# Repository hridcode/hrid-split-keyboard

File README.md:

# hrid's split keyboard

hrid's split keyboard is a sleek, custom staggered ortholinear wireless split keyboard that runs off the ESP32-S3-WROOM SMD module.

# Features

- OLED display
- EC11 rotary encoder w/ button
- Hot-swappable key switches
- Exposed circuitry look w/ acrylic top plate
- USB-C charging
- 2000mAh li-ion battery
- ESP32-S3-WROOM-1 MCU

# Photos

|Schematic|PCB|Case|
|---|---|---|
||||

# Notes

I'm not sure if this WILL work because I've heard KMK has bad support for BLE split keebs, and there may be some potential issues with the ESP32-S3-WROOM.

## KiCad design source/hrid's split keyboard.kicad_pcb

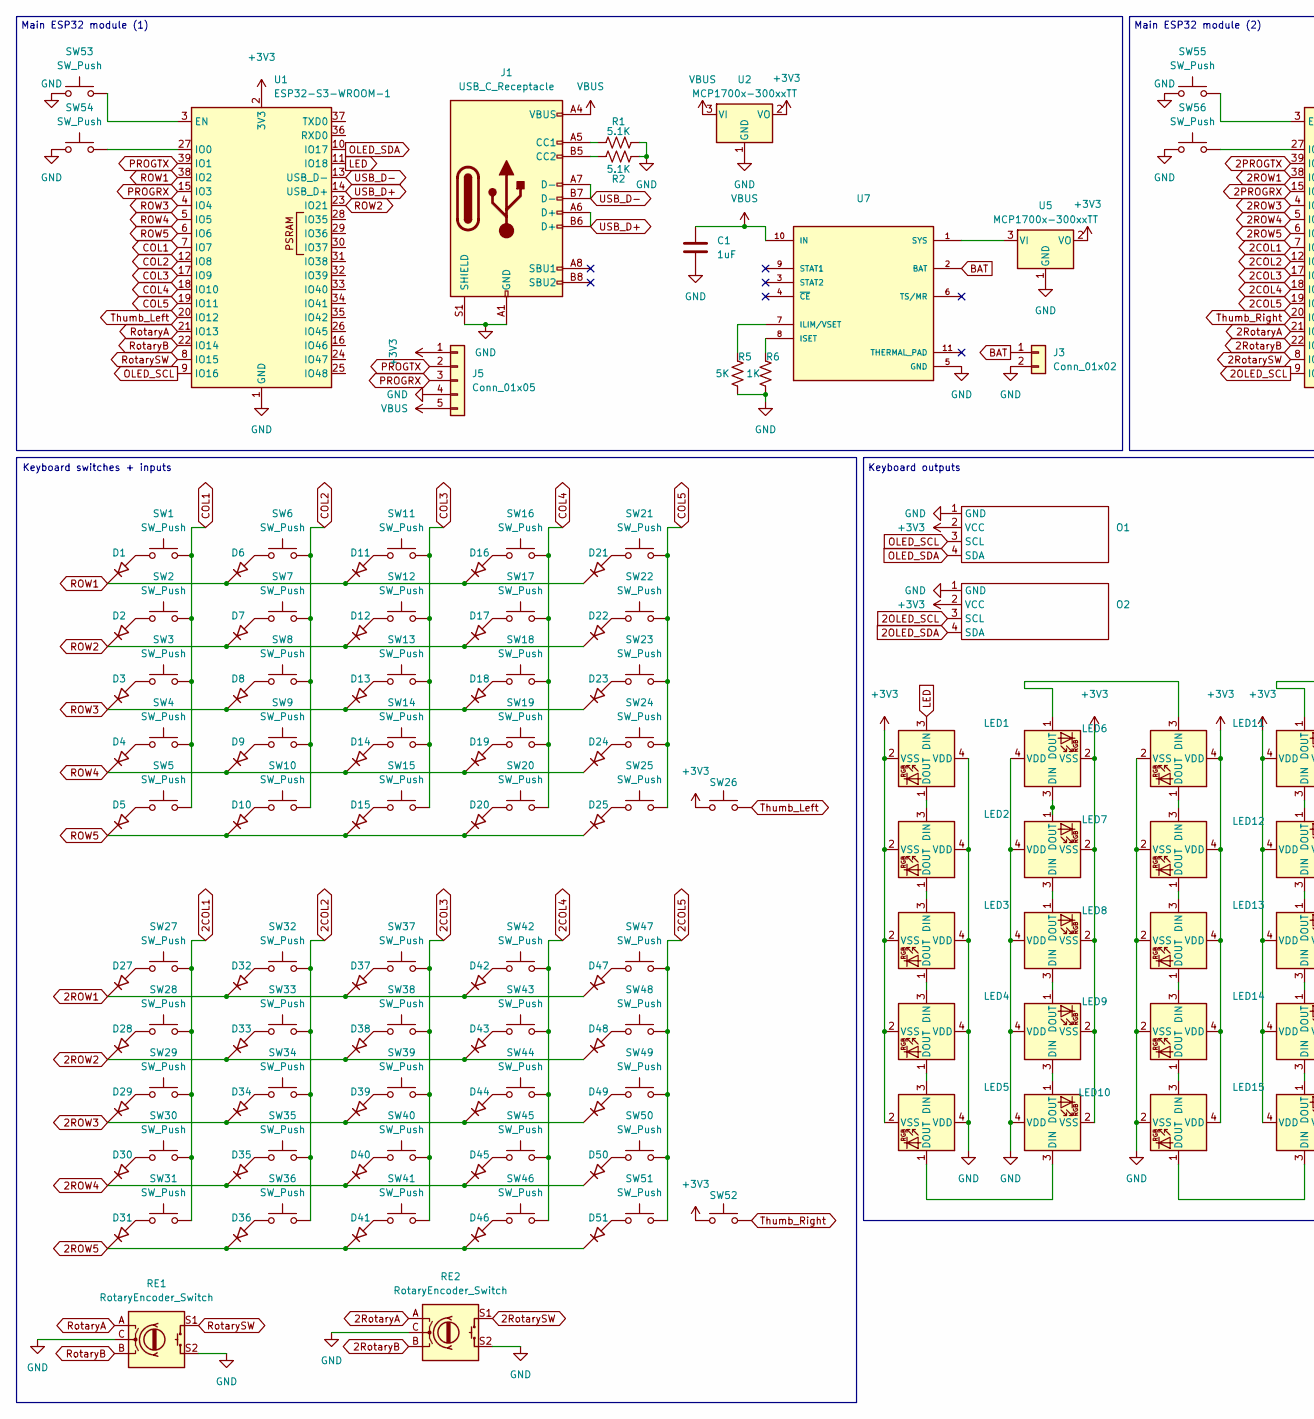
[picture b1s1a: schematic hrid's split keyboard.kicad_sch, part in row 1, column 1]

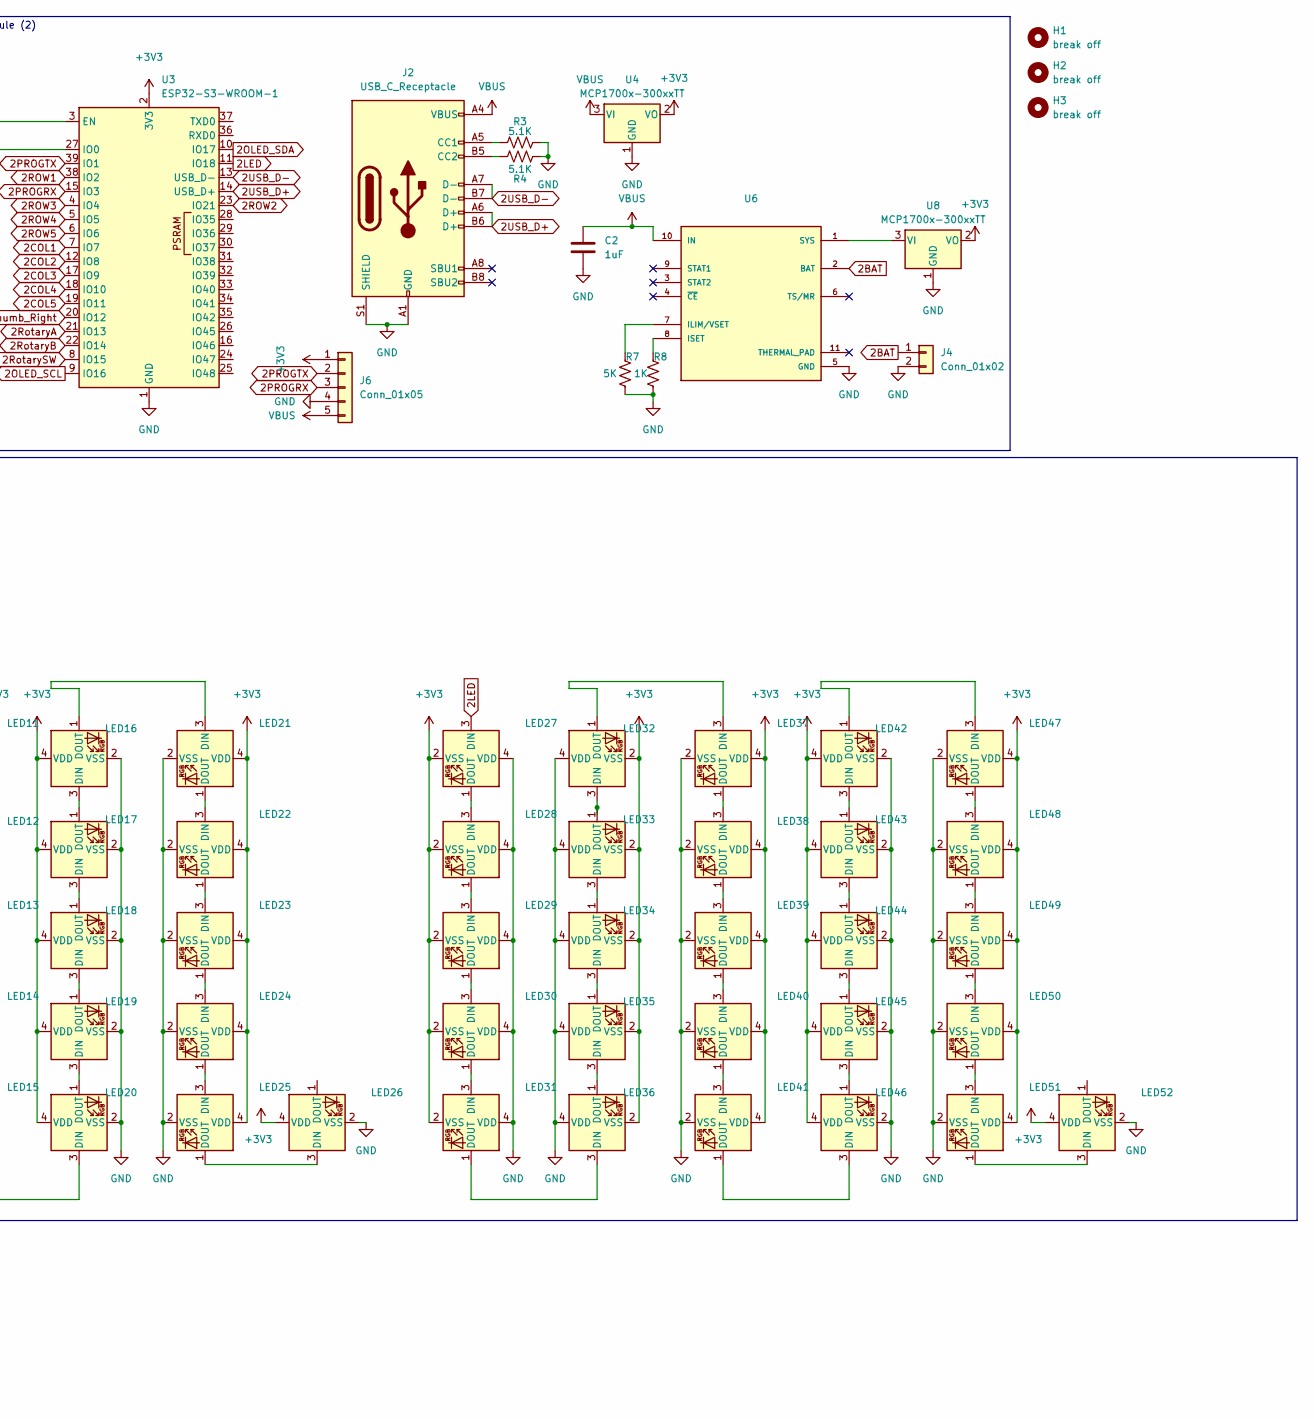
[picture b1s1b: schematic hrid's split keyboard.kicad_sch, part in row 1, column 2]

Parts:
C1, C2: 1uF; C_0603_1608Metric
D1, D2, D3, D4, D5, D6, D7, D8, D9, D10, D11, D12, D13, D14, D15, D16, D17, D18, D19, D20, D21, D22, D23, D24, D25, D27, D28, D29, D30, D31, D32, D33, D34, D35, D36, D37, D38, D39, D40, D41, D42, D43, D44, D45, D46, D47, D48, D49, D50, D51: D_45deg; D_0402_1005Metric_Pad0.77x0.64mm_HandSolder
H1, H2, H3: break off; MouseBite-Part_2.0x4.5mm_outset_D0.5mm_P0.85mm_7h
J1, J2: USB_C_Receptacle; USB_C_Receptacle_HRO_TYPE-C-31-M-12
J3, J4: Conn_01x02; JST_EH_S2B-EH_1x02_P2.50mm_Horizontal
J5, J6: Conn_01x05; PinHeader_1x05_P2.54mm_Vertical
LED1, LED2, LED3, LED4, LED5, LED6, LED7, LED8, LED9, LED10, LED11, LED12, LED13, LED14, LED15, LED16, LED17, LED18, LED19, LED20, LED21, LED22, LED23, LED24, LED25, LED26, LED27, LED28, LED29, LED30, LED31, LED32, LED33, LED34, LED35, LED36, LED37, LED38, LED39, LED40, LED41, LED42, LED43, LED44, LED45, LED46, LED47, LED48, LED49, LED50, LED51, LED52: SK6812MINI; LED_SK6812MINI_PLCC4_3.5x3.5mm_P1.75mm
O1, O2: SSD1306-4pin-0.91
R1, R2, R3, R4: 5.1K; R_0603_1608Metric
R5, R7: 5K; R_0603_1608Metric
R6, R8: 1K; R_0603_1608Metric
RE1, RE2: RotaryEncoder_Switch; RotaryEncoder_Alps_EC11E-Switch_Vertical_H20mm_MountingHoles
SW1, SW2, SW3, SW4, SW5, SW6, SW7, SW8, SW9, SW10, SW11, SW12, SW13, SW14, SW15, SW16, SW17, SW18, SW19, SW20, SW21, SW22, SW23, SW24, SW25, SW26, SW27, SW28, SW29, SW30, SW31, SW32, SW33, SW34, SW35, SW36, SW37, SW38, SW39, SW40, SW41, SW42, SW43, SW44, SW45, SW46, SW47, SW48, SW49, SW50, SW51, SW52: SW_Push; SW_MX_HotSwap_THT
SW53, SW54, SW55, SW56: SW_Push; D_2114_3652Metric
U1, U3: ESP32-S3-WROOM-1
U2, U4, U5, U8: MCP1700x-300xxTT; SOT-23
U6, U7: WSON-10-1EP_4x3mm_P0.5mm_EP2.2x2mm

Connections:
2BAT: J4.1, U6.2 (BAT)
2COL1: SW27.2, SW28.2, SW29.2, SW30.2, SW31.2, U3.7 (IO7)
2COL2: SW32.2, SW33.2, SW34.2, SW35.2, SW36.2, U3.12 (IO8)
2COL3: SW37.2, SW38.2, SW39.2, SW40.2, SW41.2, U3.17 (IO9)
2COL4: SW42.2, SW43.2, SW44.2, SW45.2, SW46.2, U3.18 (IO10)
2COL5: SW47.2, SW48.2, SW49.2, SW50.2, SW51.2, U3.19 (IO11)
2LED: LED27.3 (DIN), U3.11 (IO18)
2OLED_SCL: O2.3 (SCL), U3.9 (IO16)
2OLED_SDA: O2.4 (SDA), U3.10 (IO17)
2PROGRX: J6.3, U3.15 (IO3)
2PROGTX: J6.2, U3.39 (IO1)
2ROW1: D27.1 (K), D32.1 (K), D37.1 (K), D42.1 (K), D47.1 (K), U3.38 (IO2)
2ROW2: D28.1 (K), D33.1 (K), D38.1 (K), D43.1 (K), D48.1 (K), U3.23 (IO21)
2ROW3: D29.1 (K), D34.1 (K), D39.1 (K), D44.1 (K), D49.1 (K), U3.4 (IO4)
2ROW4: D30.1 (K), D35.1 (K), D40.1 (K), D45.1 (K), D50.1 (K), U3.5 (IO5)
2ROW5: D31.1 (K), D36.1 (K), D41.1 (K), D46.1 (K), D51.1 (K), U3.6 (IO6)
2RotaryA: RE2.A, U3.21 (IO13)
2RotaryB: RE2.B, U3.22 (IO14)
2RotarySW: RE2.S1, U3.8 (IO15)
2USB_D+: J2.A6 (D+), J2.B6 (D+), U3.14 (USB_D+)
2USB_D-: J2.A7 (D-), J2.B7 (D-), U3.13 (USB_D-)
+3V3: J5.1, J6.1, LED1.2 (VSS), LED2.2 (VSS), LED3.2 (VSS), LED4.2 (VSS), LED5.2 (VSS), LED6.2 (VSS), LED7.2 (VSS), LED8.2 (VSS), LED9.2 (VSS), LED10.2 (VSS), LED11.4 (VDD), LED12.4 (VDD), LED13.4 (VDD), LED14.4 (VDD), LED15.4 (VDD), LED16.4 (VDD), LED17.4 (VDD), LED18.4 (VDD), LED19.4 (VDD), LED20.4 (VDD), LED21.4 (VDD), LED22.4 (VDD), LED23.4 (VDD), LED24.4 (VDD), LED25.4 (VDD), LED26.4 (VDD), LED27.2 (VSS), LED28.2 (VSS), LED29.2 (VSS), LED30.2 (VSS), LED31.2 (VSS), LED32.2 (VSS), LED33.2 (VSS), LED34.2 (VSS), LED35.2 (VSS), LED36.2 (VSS), LED37.4 (VDD), LED38.4 (VDD), LED39.4 (VDD), LED40.4 (VDD), LED41.4 (VDD), LED42.4 (VDD), LED43.4 (VDD), LED44.4 (VDD), LED45.4 (VDD), LED46.4 (VDD), LED47.4 (VDD), LED48.4 (VDD), LED49.4 (VDD), LED50.4 (VDD), LED51.4 (VDD), LED52.4 (VDD), O1.2 (VCC), O2.2 (VCC), SW26.1, SW52.1, U1.2 (3V3), U2.2 (VO), U3.2 (3V3), U4.2 (VO), U5.2 (VO), U8.2 (VO)
BAT: J3.1, U7.2 (BAT)
COL1: SW1.2, SW2.2, SW3.2, SW4.2, SW5.2, U1.7 (IO7)
COL2: SW6.2, SW7.2, SW8.2, SW9.2, SW10.2, U1.12 (IO8)
COL3: SW11.2, SW12.2, SW13.2, SW14.2, SW15.2, U1.17 (IO9)
COL4: SW16.2, SW17.2, SW18.2, SW19.2, SW20.2, U1.18 (IO10)
COL5: SW21.2, SW22.2, SW23.2, SW24.2, SW25.2, U1.19 (IO11)
GND: C1.2, C2.2, J1.A1 (GND), J1.A12 (GND), J1.B1 (GND), J1.B12 (GND), J1.S1 (SHIELD), J2.A1 (GND), J2.A12 (GND), J2.B1 (GND), J2.B12 (GND), J2.S1 (SHIELD), J3.2, J4.2, J5.4, J6.4, LED1.4 (VDD), LED2.4 (VDD), LED3.4 (VDD), LED4.4 (VDD), LED5.4 (VDD), LED6.4 (VDD), LED7.4 (VDD), LED8.4 (VDD), LED9.4 (VDD), LED10.4 (VDD), LED11.2 (VSS), LED12.2 (VSS), LED13.2 (VSS), LED14.2 (VSS), LED15.2 (VSS), LED16.2 (VSS), LED17.2 (VSS), LED18.2 (VSS), LED19.2 (VSS), LED20.2 (VSS), LED21.2 (VSS), LED22.2 (VSS), LED23.2 (VSS), LED24.2 (VSS), LED25.2 (VSS), LED26.2 (VSS), LED27.4 (VDD), LED28.4 (VDD), LED29.4 (VDD), LED30.4 (VDD), LED31.4 (VDD), LED32.4 (VDD), LED33.4 (VDD), LED34.4 (VDD), LED35.4 (VDD), LED36.4 (VDD), LED37.2 (VSS), LED38.2 (VSS), LED39.2 (VSS), LED40.2 (VSS), LED41.2 (VSS), LED42.2 (VSS), LED43.2 (VSS), LED44.2 (VSS), LED45.2 (VSS), LED46.2 (VSS), LED47.2 (VSS), LED48.2 (VSS), LED49.2 (VSS), LED50.2 (VSS), LED51.2 (VSS), LED52.2 (VSS), O1.1 (GND), O2.1 (GND), R1.2, R2.2, R3.2, R4.2, R5.2, R6.2, R7.2, R8.2, RE1.C, RE1.S2, RE2.C, RE2.S2, SW53.1, SW54.1, SW55.1, SW56.1, U1.1 (GND), U1.40 (GND), U1.41 (GND), U2.1 (GND), U3.1 (GND), U3.40 (GND), U3.41 (GND), U4.1 (GND), U5.1 (GND), U6.5 (GND), U7.5 (GND), U8.1 (GND)
LED: LED1.3 (DIN), U1.11 (IO18)
unnamed: D1.2 (A), SW1.1
unnamed: D2.2 (A), SW2.1
unnamed: D3.2 (A), SW3.1
unnamed: D4.2 (A), SW4.1
unnamed: D5.2 (A), SW5.1
unnamed: D6.2 (A), SW6.1
unnamed: D7.2 (A), SW7.1
unnamed: D8.2 (A), SW8.1
unnamed: D9.2 (A), SW9.1
unnamed: D10.2 (A), SW10.1
unnamed: D11.2 (A), SW11.1
unnamed: D12.2 (A), SW12.1
unnamed: D13.2 (A), SW13.1
unnamed: D14.2 (A), SW14.1
unnamed: D15.2 (A), SW15.1
unnamed: D16.2 (A), SW16.1
unnamed: D17.2 (A), SW17.1
unnamed: D18.2 (A), SW18.1
unnamed: D19.2 (A), SW19.1
unnamed: D20.2 (A), SW20.1
unnamed: D21.2 (A), SW21.1
unnamed: D22.2 (A), SW22.1
unnamed: D23.2 (A), SW23.1
unnamed: D24.2 (A), SW24.1
unnamed: D25.2 (A), SW25.1
unnamed: D27.2 (A), SW27.1
unnamed: D28.2 (A), SW28.1
unnamed: D29.2 (A), SW29.1
unnamed: D30.2 (A), SW30.1
unnamed: D31.2 (A), SW31.1
unnamed: D32.2 (A), SW32.1
unnamed: D33.2 (A), SW33.1
unnamed: D34.2 (A), SW34.1
unnamed: D35.2 (A), SW35.1
unnamed: D36.2 (A), SW36.1
unnamed: D37.2 (A), SW37.1
unnamed: D38.2 (A), SW38.1
unnamed: D39.2 (A), SW39.1
unnamed: D40.2 (A), SW40.1
unnamed: D41.2 (A), SW41.1
unnamed: D42.2 (A), SW42.1
unnamed: D43.2 (A), SW43.1
unnamed: D44.2 (A), SW44.1
unnamed: D45.2 (A), SW45.1
unnamed: D46.2 (A), SW46.1
unnamed: D47.2 (A), SW47.1
unnamed: D48.2 (A), SW48.1
unnamed: D49.2 (A), SW49.1
unnamed: D50.2 (A), SW50.1
unnamed: D51.2 (A), SW51.1
unnamed: J1.A5 (CC1), R1.1
unnamed: J1.B5 (CC2), R2.1
unnamed: J2.A5 (CC1), R3.1
unnamed: J2.B5 (CC2), R4.1
unnamed: LED1.1 (DOUT), LED2.3 (DIN)
unnamed: LED2.1 (DOUT), LED3.3 (DIN)
unnamed: LED3.1 (DOUT), LED4.3 (DIN)
unnamed: LED4.1 (DOUT), LED5.3 (DIN)
unnamed: LED6.3 (DIN), LED7.1 (DOUT)
unnamed: LED7.3 (DIN), LED8.1 (DOUT)
unnamed: LED8.3 (DIN), LED9.1 (DOUT)
unnamed: LED5.1 (DOUT), LED10.3 (DIN)
unnamed: LED9.3 (DIN), LED10.1 (DOUT)
unnamed: LED6.1 (DOUT), LED11.3 (DIN)
unnamed: LED11.1 (DOUT), LED12.3 (DIN)
unnamed: LED12.1 (DOUT), LED13.3 (DIN)
unnamed: LED13.1 (DOUT), LED14.3 (DIN)
unnamed: LED14.1 (DOUT), LED15.3 (DIN)
unnamed: LED15.1 (DOUT), LED20.3 (DIN)
unnamed: LED16.3 (DIN), LED17.1 (DOUT)
unnamed: LED16.1 (DOUT), LED21.3 (DIN)
unnamed: LED17.3 (DIN), LED18.1 (DOUT)
unnamed: LED18.3 (DIN), LED19.1 (DOUT)
unnamed: LED19.3 (DIN), LED20.1 (DOUT)
unnamed: LED21.1 (DOUT), LED22.3 (DIN)
unnamed: LED22.1 (DOUT), LED23.3 (DIN)
unnamed: LED23.1 (DOUT), LED24.3 (DIN)
unnamed: LED24.1 (DOUT), LED25.3 (DIN)
unnamed: LED25.1 (DOUT), LED26.3 (DIN)
unnamed: LED27.1 (DOUT), LED28.3 (DIN)
unnamed: LED28.1 (DOUT), LED29.3 (DIN)
unnamed: LED29.1 (DOUT), LED30.3 (DIN)
unnamed: LED30.1 (DOUT), LED31.3 (DIN)
unnamed: LED31.1 (DOUT), LED36.3 (DIN)
unnamed: LED32.3 (DIN), LED33.1 (DOUT)
unnamed: LED32.1 (DOUT), LED37.3 (DIN)
unnamed: LED33.3 (DIN), LED34.1 (DOUT)
unnamed: LED34.3 (DIN), LED35.1 (DOUT)
unnamed: LED35.3 (DIN), LED36.1 (DOUT)
unnamed: LED37.1 (DOUT), LED38.3 (DIN)
unnamed: LED38.1 (DOUT), LED39.3 (DIN)
unnamed: LED39.1 (DOUT), LED40.3 (DIN)
unnamed: LED40.1 (DOUT), LED41.3 (DIN)
unnamed: LED41.1 (DOUT), LED46.3 (DIN)
unnamed: LED42.3 (DIN), LED43.1 (DOUT)
unnamed: LED42.1 (DOUT), LED47.3 (DIN)
unnamed: LED43.3 (DIN), LED44.1 (DOUT)
unnamed: LED44.3 (DIN), LED45.1 (DOUT)
unnamed: LED45.3 (DIN), LED46.1 (DOUT)
unnamed: LED47.1 (DOUT), LED48.3 (DIN)
unnamed: LED48.1 (DOUT), LED49.3 (DIN)
unnamed: LED49.1 (DOUT), LED50.3 (DIN)
unnamed: LED50.1 (DOUT), LED51.3 (DIN)
unnamed: LED51.1 (DOUT), LED52.3 (DIN)
unnamed: SW53.2, U1.3 (EN)
unnamed: SW54.2, U1.27 (IO0)
unnamed: SW55.2, U3.3 (EN)
unnamed: SW56.2, U3.27 (IO0)
unnamed: U5.3 (VI), U7.1 (SYS)
unnamed: R7.1, U6.7 (ILIM/VSET)
unnamed: R8.1, U6.8 (ISET)
unnamed: U6.1 (SYS), U8.3 (VI)
unnamed: R5.1, U7.7 (ILIM/VSET)
unnamed: R6.1, U7.8 (ISET)
OLED_SCL: O1.3 (SCL), U1.9 (IO16)
OLED_SDA: O1.4 (SDA), U1.10 (IO17)
PROGRX: J5.3, U1.15 (IO3)
PROGTX: J5.2, U1.39 (IO1)
ROW1: D1.1 (K), D6.1 (K), D11.1 (K), D16.1 (K), D21.1 (K), U1.38 (IO2)
ROW2: D2.1 (K), D7.1 (K), D12.1 (K), D17.1 (K), D22.1 (K), U1.23 (IO21)
ROW3: D3.1 (K), D8.1 (K), D13.1 (K), D18.1 (K), D23.1 (K), U1.4 (IO4)
ROW4: D4.1 (K), D9.1 (K), D14.1 (K), D19.1 (K), D24.1 (K), U1.5 (IO5)
ROW5: D5.1 (K), D10.1 (K), D15.1 (K), D20.1 (K), D25.1 (K), U1.6 (IO6)
RotaryA: RE1.A, U1.21 (IO13)
RotaryB: RE1.B, U1.22 (IO14)
RotarySW: RE1.S1, U1.8 (IO15)
Thumb_Left: SW26.2, U1.20 (IO12)
Thumb_Right: SW52.2, U3.20 (IO12)
USB_D+: J1.A6 (D+), J1.B6 (D+), U1.14 (USB_D+)
USB_D-: J1.A7 (D-), J1.B7 (D-), U1.13 (USB_D-)
VBUS: C1.1, C2.1, J1.A4 (VBUS), J1.A9 (VBUS), J1.B4 (VBUS), J1.B9 (VBUS), J2.A4 (VBUS), J2.A9 (VBUS), J2.B4 (VBUS), J2.B9 (VBUS), J5.5, J6.5, U2.3 (VI), U4.3 (VI), U6.10 (IN), U7.10 (IN)

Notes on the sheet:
Main ESP32 module (1)
Keyboard switches + inputs
Keyboard outputs
Main ESP32 module (2)

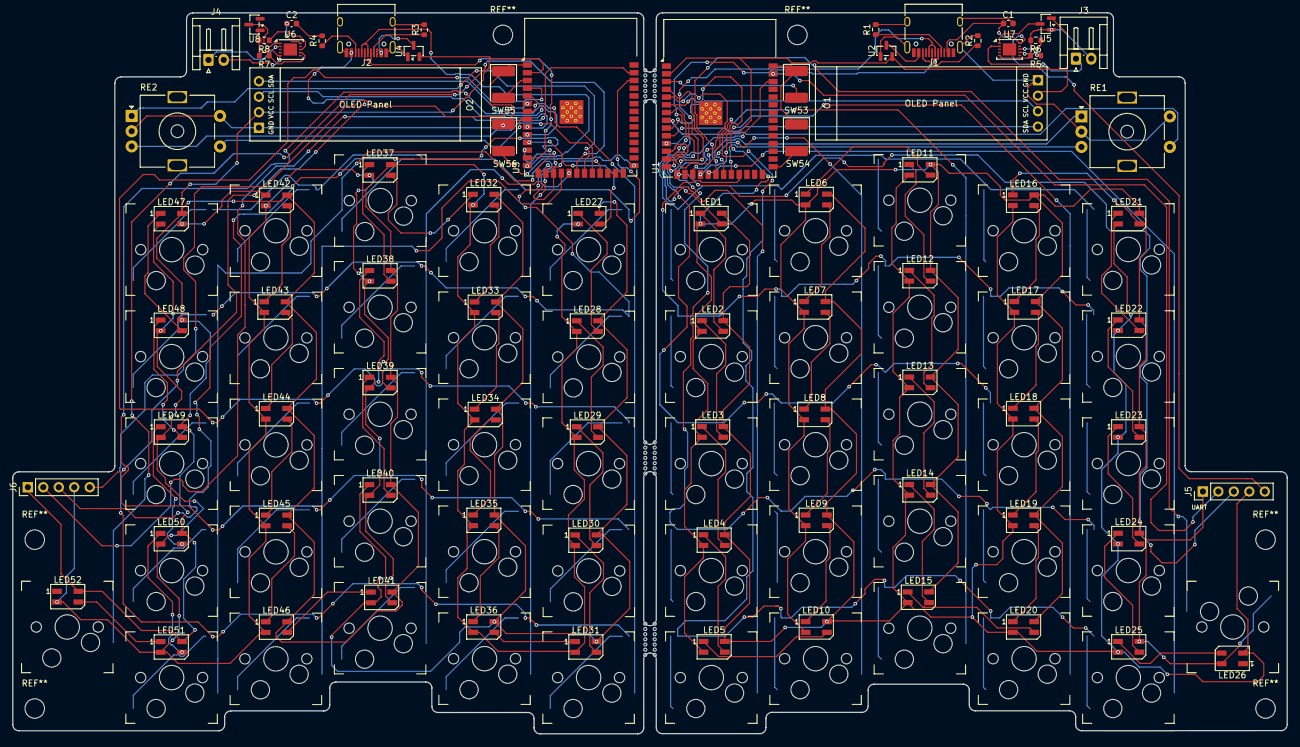
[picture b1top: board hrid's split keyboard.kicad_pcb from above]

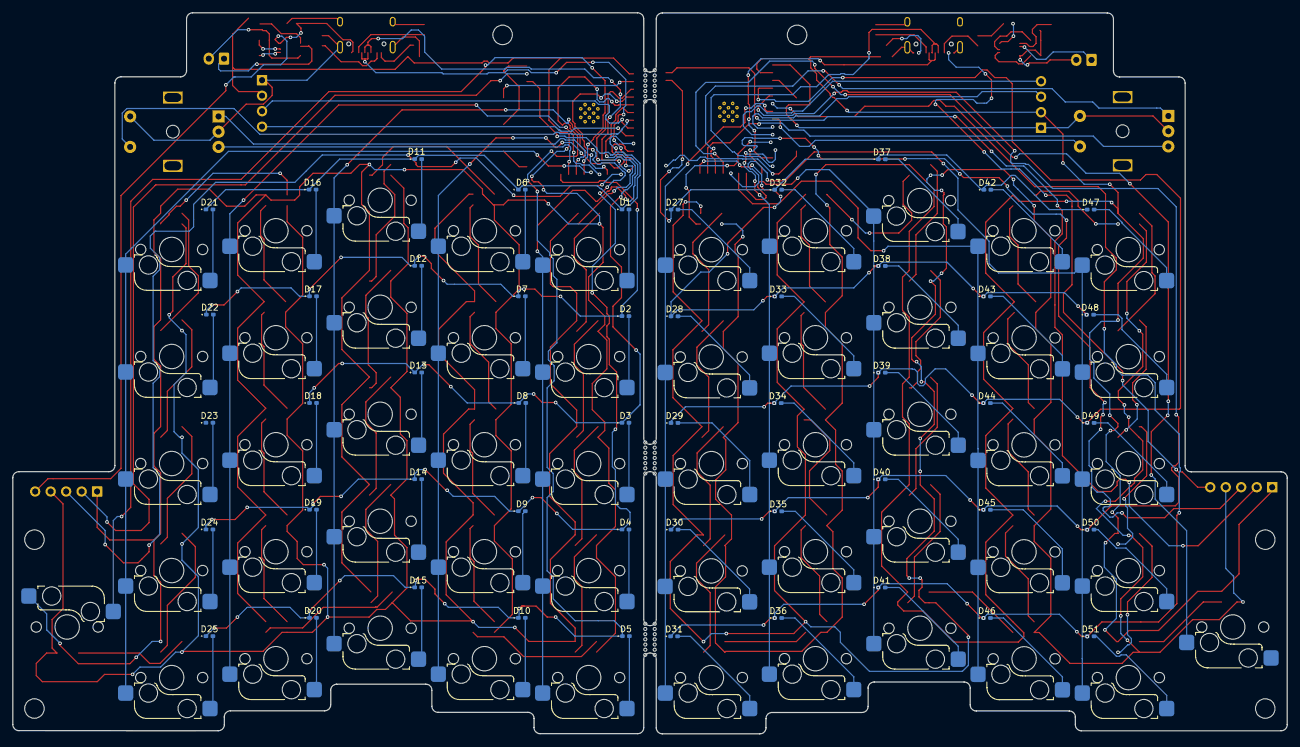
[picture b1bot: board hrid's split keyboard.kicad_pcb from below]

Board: 2 copper layers, 209.1 x 118.3 mm, 192 parts (50 on the bottom side), 161 nets.

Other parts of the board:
H1#2, H2#2, H3#2: break off; MouseBite-Part_2.0x4.5mm_outset_D0.5mm_P0.85mm_7h

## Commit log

2026-04-20 Added production and source
2026-04-20 Updated README.md and added photos
